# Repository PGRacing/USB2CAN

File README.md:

# USB2CAN

### This solution is created to communicate with custom CANBUS devices by USB to PC (windows). The reasoning of the device creation is Formula Student bolide managment. Device is based on STM32F103 and MCP2561 and USB-FS (on USB-C connector).

##### TODO: 
1. Fix the USB-C header
2. Fix the 5V LDO enable pin

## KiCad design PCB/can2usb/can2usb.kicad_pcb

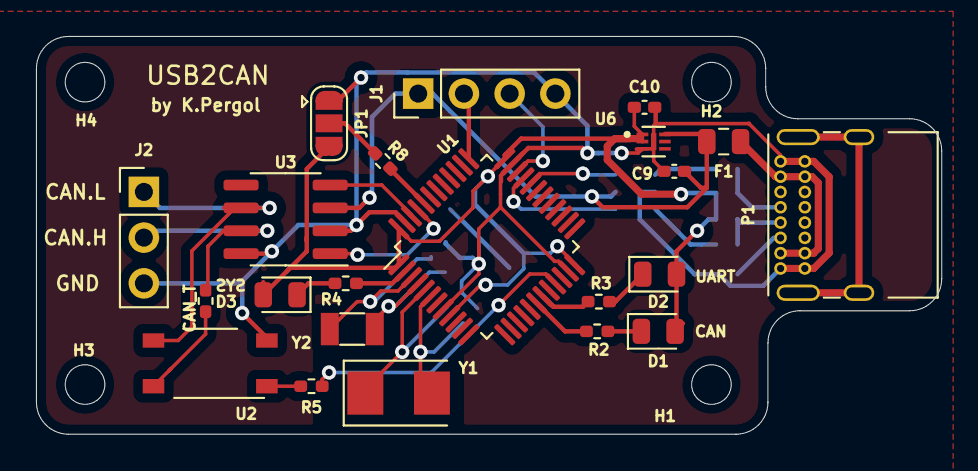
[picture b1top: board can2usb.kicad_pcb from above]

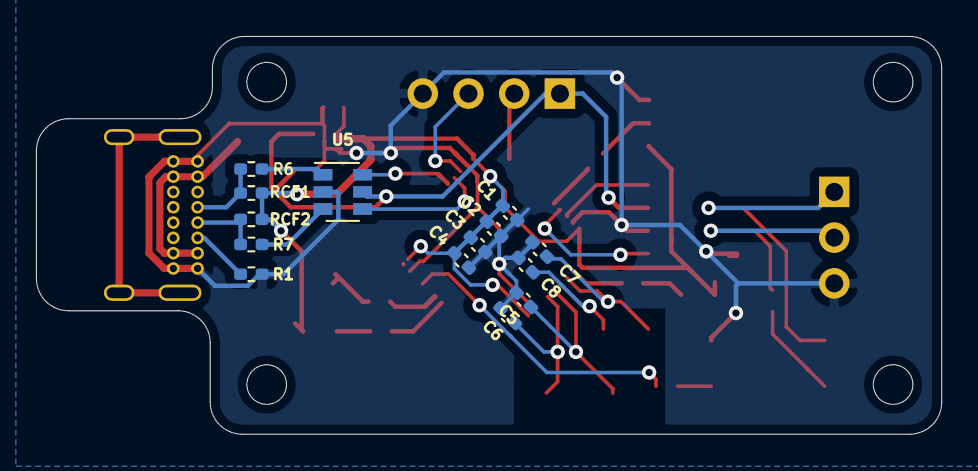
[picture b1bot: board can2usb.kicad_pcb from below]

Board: 2 copper layers, 50.3 x 22.1 mm, 40 parts (14 on the bottom side), 32 nets.

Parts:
C1, C2, C3, C4: 100n; C_0402_1005Metric_Pad0.74x0.62mm_HandSolder
C5, C6, C7, C8: 22pF; C_0402_1005Metric_Pad0.74x0.62mm_HandSolder
C9, C10: 10uF; C_0402_1005Metric_Pad0.74x0.62mm_HandSolder
CAN_T: 100; R_0402_1005Metric_Pad0.72x0.64mm_HandSolder
D1, D2, D3: BUILTIN_LED; LED_0805_2012Metric
F1: 300mA; Fuse_0805_2012Metric
H1, H2, H3, H4: MountingHole; MountingHole_2.2mm_M2
J1: STLINK; PinHeader_1x04_P2.54mm_Vertical
J2: Conn_01x03_Male; PinHeader_1x03_P2.54mm_Vertical
JP1: SolderJumper_3_Open; SolderJumper-3_P1.3mm_Open_RoundedPad1.0x1.5mm
P1: USB_C_Plug_USB2.0; USB_C_Receptacle_GCT_USB4085
R1: 5.1k; R_0402_1005Metric_Pad0.72x0.64mm_HandSolder
R2, R3, R4: 510; R_0402_1005Metric_Pad0.72x0.64mm_HandSolder
R5, R8: 1k; R_0402_1005Metric_Pad0.72x0.64mm_HandSolder
R6, R7: 22; R_0402_1005Metric_Pad0.72x0.64mm_HandSolder
RCF1: 0; R_0402_1005Metric_Pad0.72x0.64mm_HandSolder
RCF2: 1k5; R_0402_1005Metric_Pad0.72x0.64mm_HandSolder
U1: STM32F103C6Tx; LQFP-48_7x7mm_P0.5mm
U2: TLP175A; MFSOP6-4_4.4x3.6mm_P1.27mm
U3: MCP2561-E-SN; SOIC-8_3.9x4.9mm_P1.27mm
U5: USBLC6-2SC6; SOT-23-6
U6: MIC5528-3.3YMT-TR; SON40P120X120X60-7N
Y1: 16MHz; Crystal_SMD_5032-2Pin_5.0x3.2mm
Y2: 32KHz; Crystal_SMD_3215-2Pin_3.2x1.5mm

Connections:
+3V3: C1.1, C2.1, C3.1, C4.1, C10.2, D1.2, D2.2, D3.2, JP1.3, RCF1.2, RCF2.2, U1.1, U1.9, U1.24, U1.36, U1.48, U6.1, U6.2
+5V: C9.2, F1.2, J1.1, U3.3, U5.5, U6.6
BOOT0: R8.1, U1.44
B_LED: R4.2, U1.2
CAN_H: CAN_T.1, J2.2, U3.7
CAN_L: J2.1, U2.4, U3.6
CAN_LED: R2.2, U1.18
CAN_RX: U1.45, U3.1
CAN_TX: U1.46, U3.4
GND: C1.2, C2.2, C3.2, C4.2, C5.2, C6.2, C7.2, C8.2, C9.1, C10.1, J1.4, J2.3, JP1.1, P1.A1, P1.A12, P1.B1, P1.B12, R1.2, U1.8, U1.23, U1.35, U1.47, U2.3, U3.2, U3.8, U5.2, U6.3, U6.7
L_OSC_IN: C7.1, U1.3, Y2.1
L_OSC_OUT: C8.1, U1.4, Y2.2
unnamed: D1.1, R2.1
unnamed: D2.1, R3.1
unnamed: D3.1, R4.1
unnamed: F1.1, P1.A4, P1.A9, P1.B4, P1.B9
unnamed: JP1.2, R8.2
unnamed: P1.A5, R1.1
unnamed: P1.A6, R7.1, RCF2.1
unnamed: P1.A7, R6.2, RCF1.1
unnamed: R5.2, U2.1
unnamed: CAN_T.2, U2.6
OSC_IN: C5.1, U1.5, Y1.1
OSC_OUT: C6.1, U1.6, Y1.2
SWCLK: J1.2, U1.37
SWDIO: J1.3, U1.34
TERMINATOR_SW: R5.1, U1.21
UART_LED: R3.2, U1.19
USB_CONN_D+: R7.2, U5.3
USB_CONN_D-: R6.1, U5.1
USB_D+: U1.33, U5.4
USB_D-: U1.32, U5.6

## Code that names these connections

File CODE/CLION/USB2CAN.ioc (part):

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Mcu.Name=STM32F103C(8-B)Tx
Mcu.Package=LQFP48
Mcu.UserName=STM32F103CBTx
PA11.Mode=Device
PA11.Signal=USB_DM
PA12.Mode=Device
PA12.Signal=USB_DP
PB10.GPIOParameters=GPIO_Label
PB10.GPIO_Label=TERMIANTOR_SW
PB10.Signal=GPIO_Output
PB8.Mode=CAN_Activate
PB8.Signal=CAN_RX
PB9.Mode=CAN_Activate
PB9.Signal=CAN_TX
PC13-TAMPER-RTC.GPIOParameters=GPIO_Label
PC13-TAMPER-RTC.GPIO_Label=B_LED
PC13-TAMPER-RTC.Signal=GPIO_Output
PC14-OSC32_IN.Mode=LSE-External-Oscillator
PC14-OSC32_IN.Signal=RCC_OSC32_IN
PC15-OSC32_OUT.Mode=LSE-External-Oscillator
PC15-OSC32_OUT.Signal=RCC_OSC32_OUT
PD0-OSC_IN.Mode=HSE-External-Oscillator
PD0-OSC_IN.Signal=RCC_OSC_IN
PD1-OSC_OUT.Mode=HSE-External-Oscillator
PD1-OSC_OUT.Signal=RCC_OSC_OUT
RCC.HSEDivPLL=RCC_HSE_PREDIV_DIV2
RCC.HSE_VALUE=16000000
RCC.SYSCLKFreq_VALUE=72000000
RCC.SYSCLKSource=RCC_SYSCLKSOURCE_PLLCLK
board=custom

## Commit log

2022-10-07 Initial commit /w PCB
2022-10-07 First version pcb
2022-10-09 Finished brd
2022-10-09 Minor chnages
2022-10-09 Minor chnages in PCB layout
2022-10-14 New PCB design with 0402 and smaller LDO
2022-10-14 Added 0402 and MIC5528
2022-10-15 New PCB design
2022-10-15 Minor changes in PCB desing
2022-12-10 Initial code commit
2022-12-10 PCB modifications after production
2023-02-07 Added new CLION code
2023-02-08 Added new clion code, but CAN and USB not working simulatniously
2023-06-25 Added notification about button hold
2023-06-25 Local code copy
2024-02-04 Create PC_APP
2024-02-04 adding app
2024-02-04 second attempt
2024-02-08 addition of byte selection
2024-02-12 Add .gitignore
2024-02-12 Remove build files
2024-02-22 some changes
2024-02-26 addition of port selection
2024-10-01 improving the performance and appearance of the application
2024-12-13 Qt app
